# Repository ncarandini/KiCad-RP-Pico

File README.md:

# KiCad-RP-Pico
A simple repository of files needed to add a 3D footprint of the Raspberry Pi Pico board to KiCad.

## Schematic and footprint
I've started from the schematics and footprint files available on the [HeadBoffin RP_Silicon_KiCad GitHub project](https://github.com/HeadBoffin/RP_Silicon_KiCad). Because there are some errors in the readme file on how and where we can get those files from the Raspberry Pi web site, I've copied the needed files here, on the `RP-Pico Libraries` folder. Follow the [install instructions](Install%20instructions.md) to add the Raspberry Pi Pico board schema and footprint to a KiCad project:

## 3D Visual
Elas, with the files found in the [HeadBoffin project](https://github.com/HeadBoffin/RP_Silicon_KiCad) no visual footprint is available, as we can see on the 3D viewer:

So I decided to create one, using the mechanical specification from the [Raspberry Pi Pico datasheet](https://datasheets.raspberrypi.org/pico/pico-datasheet.pdf):

I've used SketchUp to create the 3D model:

and I used the native Sketchup export function (no plugin needed) to create the VRLM file `Pico.wrl` that I've also added an the  `RP-Pico Libraries` folder, as the VRLM format is one of the 3D model format that KiCad allow to use for the visual representation of a CPB footprint.

After adding it to the Raspberry Pi Pico KiCad footprint library, we can finally see the visual representation of the Raspberry Pi Pico board:

Please note that the castellated pins of the Pico board allow it to be usable as a surface mount module. That's way you see the board simply placed on top of the PCB board.

## Install 3D visual

Please note that adding the visual file to the footprint make the use of KiCad very slow when showing the 3D viewer for the first time. On my old laptop it takes 30s to show, but only 3s to reopen it. The good news are that you can disable it while working at your project and enable it when you want a nice 3D representation of your work.

To install and enable/disable it follow the [install instructions](Install%20instructions.md).

## Test project

I've created a test project where you can find a simple usage example. The first image of this readme shows the result.

A tweet with an image of your Raspberry Pi Pico project with a link this project and me (@tpcware) would be greatly appreciated.

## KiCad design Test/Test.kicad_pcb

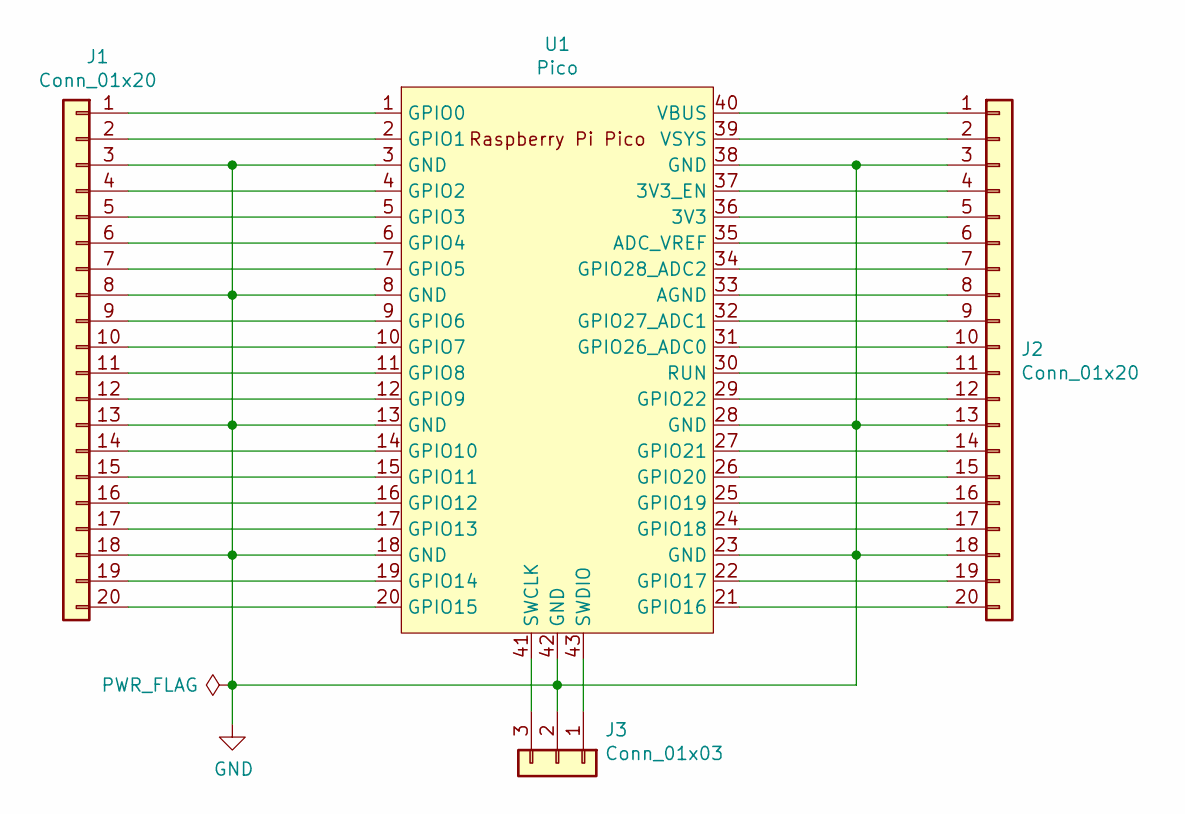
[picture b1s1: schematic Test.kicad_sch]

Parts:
J1, J2: Conn_01x20; PinSocket_1x20_P1.00mm_Vertical
J3: Conn_01x03; PinSocket_1x03_P1.00mm_Vertical
U1: Pico; RPi_Pico_SMD_TH

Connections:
GND: J1.3, J1.8, J1.13, J1.18, J2.3, J2.13, J2.18, J3.2, U1.3 (GND), U1.8 (GND), U1.13 (GND), U1.18 (GND), U1.23 (GND), U1.28 (GND), U1.38 (GND), U1.42 (GND)
unnamed: J1.1, U1.1 (GPIO0)
unnamed: J1.2, U1.2 (GPIO1)
unnamed: J1.4, U1.4 (GPIO2)
unnamed: J1.5, U1.5 (GPIO3)
unnamed: J1.6, U1.6 (GPIO4)
unnamed: J1.7, U1.7 (GPIO5)
unnamed: J1.9, U1.9 (GPIO6)
unnamed: J1.10, U1.10 (GPIO7)
unnamed: J1.11, U1.11 (GPIO8)
unnamed: J1.12, U1.12 (GPIO9)
unnamed: J1.14, U1.14 (GPIO10)
unnamed: J1.15, U1.15 (GPIO11)
unnamed: J1.16, U1.16 (GPIO12)
unnamed: J1.17, U1.17 (GPIO13)
unnamed: J1.19, U1.19 (GPIO14)
unnamed: J1.20, U1.20 (GPIO15)
unnamed: J2.1, U1.40 (VBUS)
unnamed: J2.2, U1.39 (VSYS)
unnamed: J2.4, U1.37 (3V3_EN)
unnamed: J2.5, U1.36 (3V3)
unnamed: J2.6, U1.35 (ADC_VREF)
unnamed: J2.7, U1.34 (GPIO28_ADC2)
unnamed: J2.8, U1.33 (AGND)
unnamed: J2.9, U1.32 (GPIO27_ADC1)
unnamed: J2.10, U1.31 (GPIO26_ADC0)
unnamed: J2.11, U1.30 (RUN)
unnamed: J2.12, U1.29 (GPIO22)
unnamed: J2.14, U1.27 (GPIO21)
unnamed: J2.15, U1.26 (GPIO20)
unnamed: J2.16, U1.25 (GPIO19)
unnamed: J2.17, U1.24 (GPIO18)
unnamed: J2.19, U1.22 (GPIO17)
unnamed: J2.20, U1.21 (GPIO16)
unnamed: J3.1, U1.43 (SWDIO)
unnamed: J3.3, U1.41 (SWCLK)

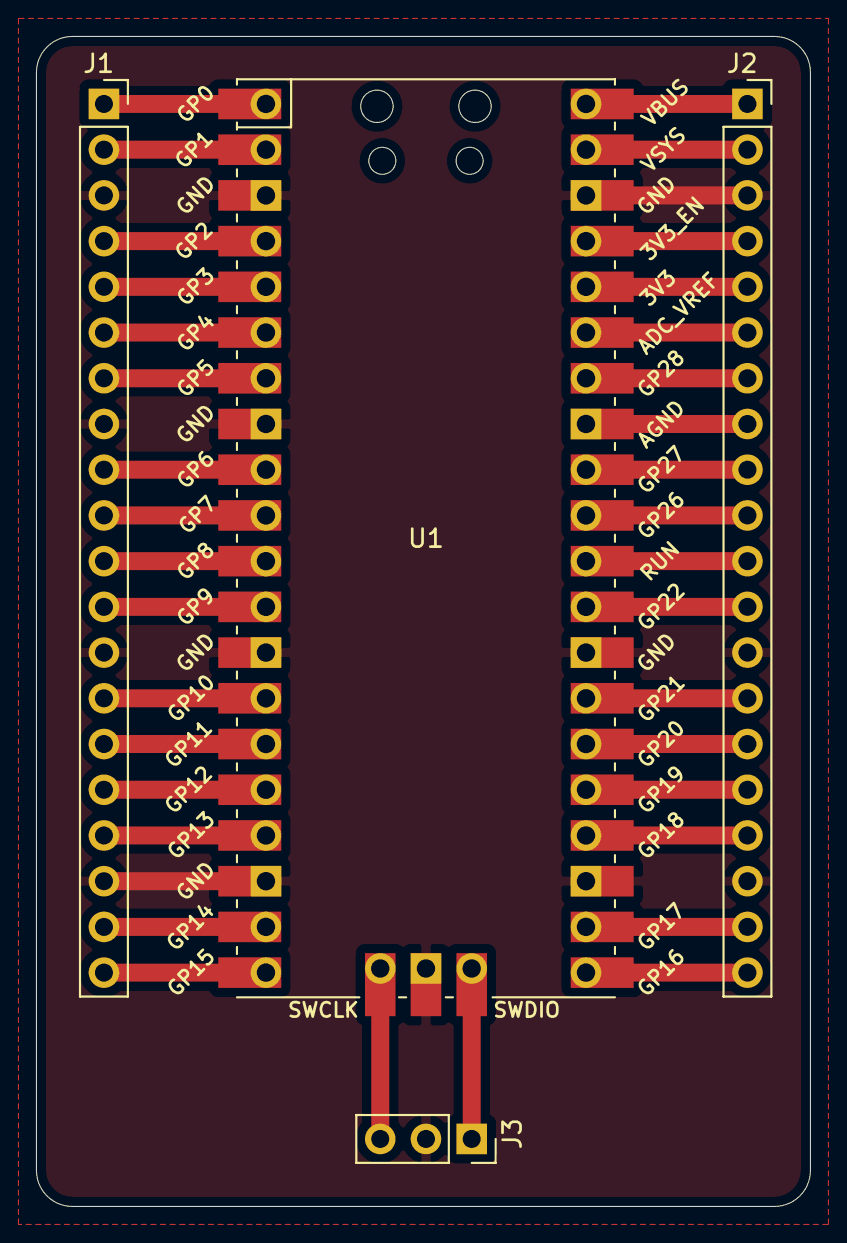
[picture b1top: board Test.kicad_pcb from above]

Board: 2 copper layers, 43.0 x 65.0 mm, 4 parts (0 on the bottom side), 36 nets.

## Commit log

2021-02-16 Vers. 0.1
2021-02-17 Add readme with images
2021-02-17 Add KiCad test project
2021-02-17 Add Install instructions file
2021-02-17 Fix readme
2021-02-17 Update readme and related images
2021-02-17 Add license link to the readme
2021-02-18 Update install instructions with photo
2021-03-07 Add SketchUp Model
2021-08-04 fix image04 name
2021-08-05 Fix scale and translation of wrl file
2021-08-05 Fix Issues #2 (pins classific) and #3 (comp name)
2021-08-11 Update install readme
2021-08-11 Fix typo on install readme
2021-08-11 Fix typo
2022-02-03 Migrating library to kicad_sym for KiCad 6
2022-03-06 Remove obsolete .lib file replaced by .kicad_sym
2022-03-06 Remove old files
2022-03-06 Add new (updated to KiCad 6) files
2022-03-06 Update images to KiCad 6
2022-03-06 Update to KiCad 6
2022-03-06 Fix pcb file
2022-06-01 rename: 3v3 (pin36) --> power output; GND (pin38) --> power input
2022-06-20 Use project relative paths
    This reduces the install instruction to 3 simple steps.
    Add a Git submodule to your KiCad project:
    ```
    git submodule add https://github.com/ncarandini/KiCad-RP-Pico
    ```
    Create a file `sym-lib-table` with:
2022-09-22 Modifying the design to provide both through-hole-only variant (still labeled) and smd-only variant (sans holes and wasting opposite layer.
2022-09-27 noSWD variants as well - to simplify routing etc...
2022-10-10 Change direction of 3v3 pin
2022-10-10 More fixes to provided layout
2022-10-11 VREF is an input, not actively powering
2023-03-21 Update MCU_RaspberryPi_and_Boards.kicad_sym
    Changed a GND pin from bidirectional to power_in
2023-04-30 Added SMD-only RPi Pico footprint.
